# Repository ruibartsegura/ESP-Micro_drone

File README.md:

# ESP Micro Drone
## Intro
Development of a micro drone based on an ESP platform, adapted and extended through the integration of ROS 2. It uses an ESP32-S2 mini as flight controller and talks to a ROS 2 computer over WiFi with micro-ROS. </br>

</br>

## Repository

| Folder | What it is |
|--------|------------|
| [`code/`](https://github.com/ruibartsegura/ESP-Micro_drone/tree/main/code) | Firmware of the ESP32-S2 (ESP-IDF + micro-ROS), host unit tests and the ROS 2 workspace. |
| [`PCB_design/`](https://github.com/ruibartsegura/ESP-Micro_drone/tree/main/PCB_design) | KiCad project of the drone PCB, with the files to manufacture it. |
| `Hardware_Design/` | FreeCAD models of the frame, motors, blades and the complete drone. |
| `img/` | Images used in the READMEs. |

## [PCB Design](https://github.com/ruibartsegura/ESP-Micro_drone/tree/main/PCB_design)
The PCB is the frame of the drone. The ESP32-S2 mini and a GY-87 sensor board (MPU-6050 + BMP180) are plugged into it, and it has the drivers of the 4 motors, the 3.3 V regulator, the battery connector and the status LEDs.

## [Code](https://github.com/ruibartsegura/ESP-Micro_drone/tree/main/code)
The firmware runs every part of the drone as a FreeRTOS task: sensors, state machine, cascade PID controller, odometry and the micro-ROS node. The same firmware can also fly a simulated drone in Gazebo, so the controller can be tested before flying the real one. See [`code/README.md`](code/README.md) to build, flash and fly it.

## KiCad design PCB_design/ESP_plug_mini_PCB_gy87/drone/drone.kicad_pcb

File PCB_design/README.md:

# PCB design

Here you can find the design of the drone PCB, made with KiCad.

## [Plug mini PCB (GY-87)](https://github.com/ruibartsegura/ESP-Micro_drone/tree/main/PCB_design/ESP_plug_mini_PCB_gy87/drone)

The PCB is also the frame of the drone. The boards are not soldered on it, they are plugged in:

- **ESP32-S2 mini** (Wemos S2 Mini), on two 2x8 pin sockets.
- **GY-87** sensor board, on a 1x8 header. The firmware uses its MPU-6050 (accelerometer + gyroscope) and its BMP180 (barometer).

The board also has:

- 4 MOSFET drivers (AO3400A) for the motors.
- 3.3 V regulator (AP2112K-3.3).
- JST-PH connector for the battery.
- Status LEDs and a push button.

### Files

| File | What it is |
|------|------------|
| `drone.kicad_pro`, `drone.kicad_sch`, `drone.kicad_pcb` | KiCad project, schematic and PCB. |
| `*.pretty/`, `fp-lib-table` | Custom footprints used by the PCB. |
| `production/` | Files to manufacture it: Gerbers (`production/drone/`), `BOM.csv`, pick and place (`drone-all.pos`) and the 3D model (`drone.step`). |

The 3D models of the ESP32-S2 mini and the GY-87 are in [`extra_step_files/`](https://github.com/ruibartsegura/ESP-Micro_drone/tree/main/PCB_design/extra_step_files).

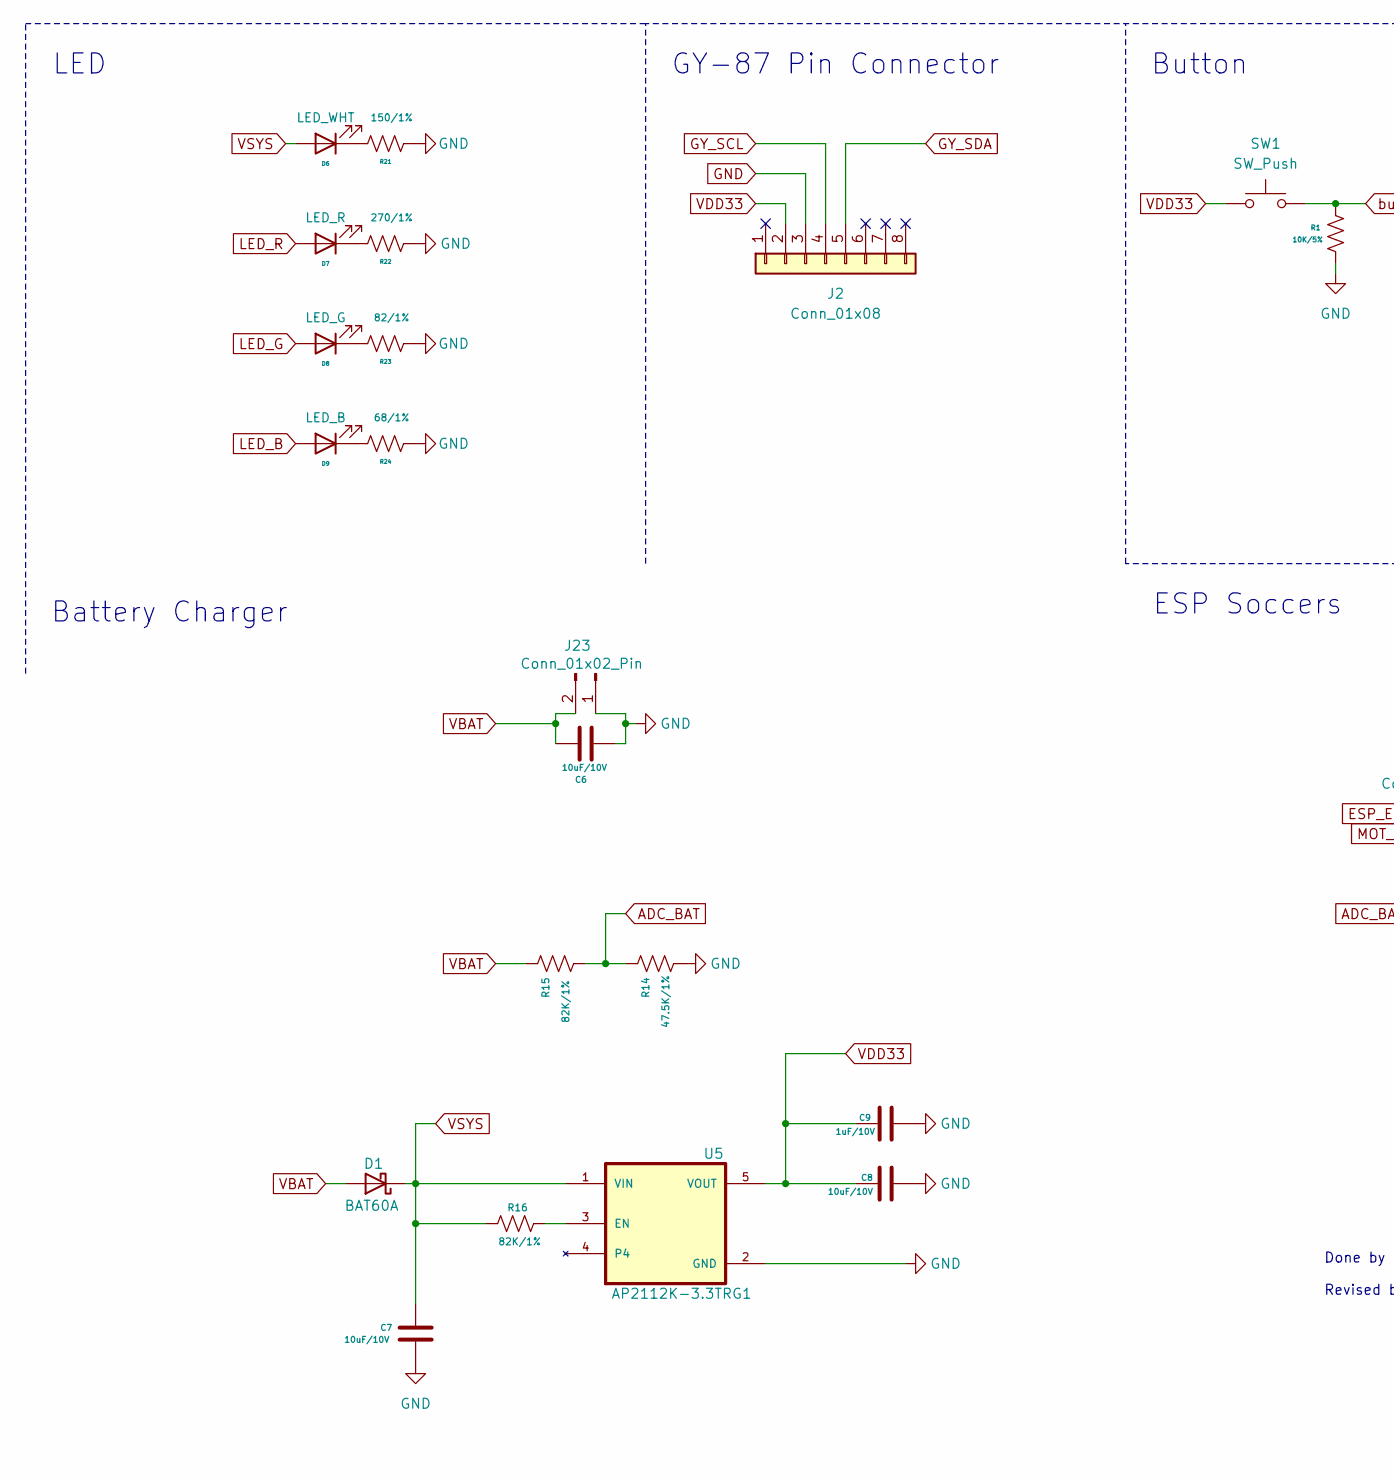
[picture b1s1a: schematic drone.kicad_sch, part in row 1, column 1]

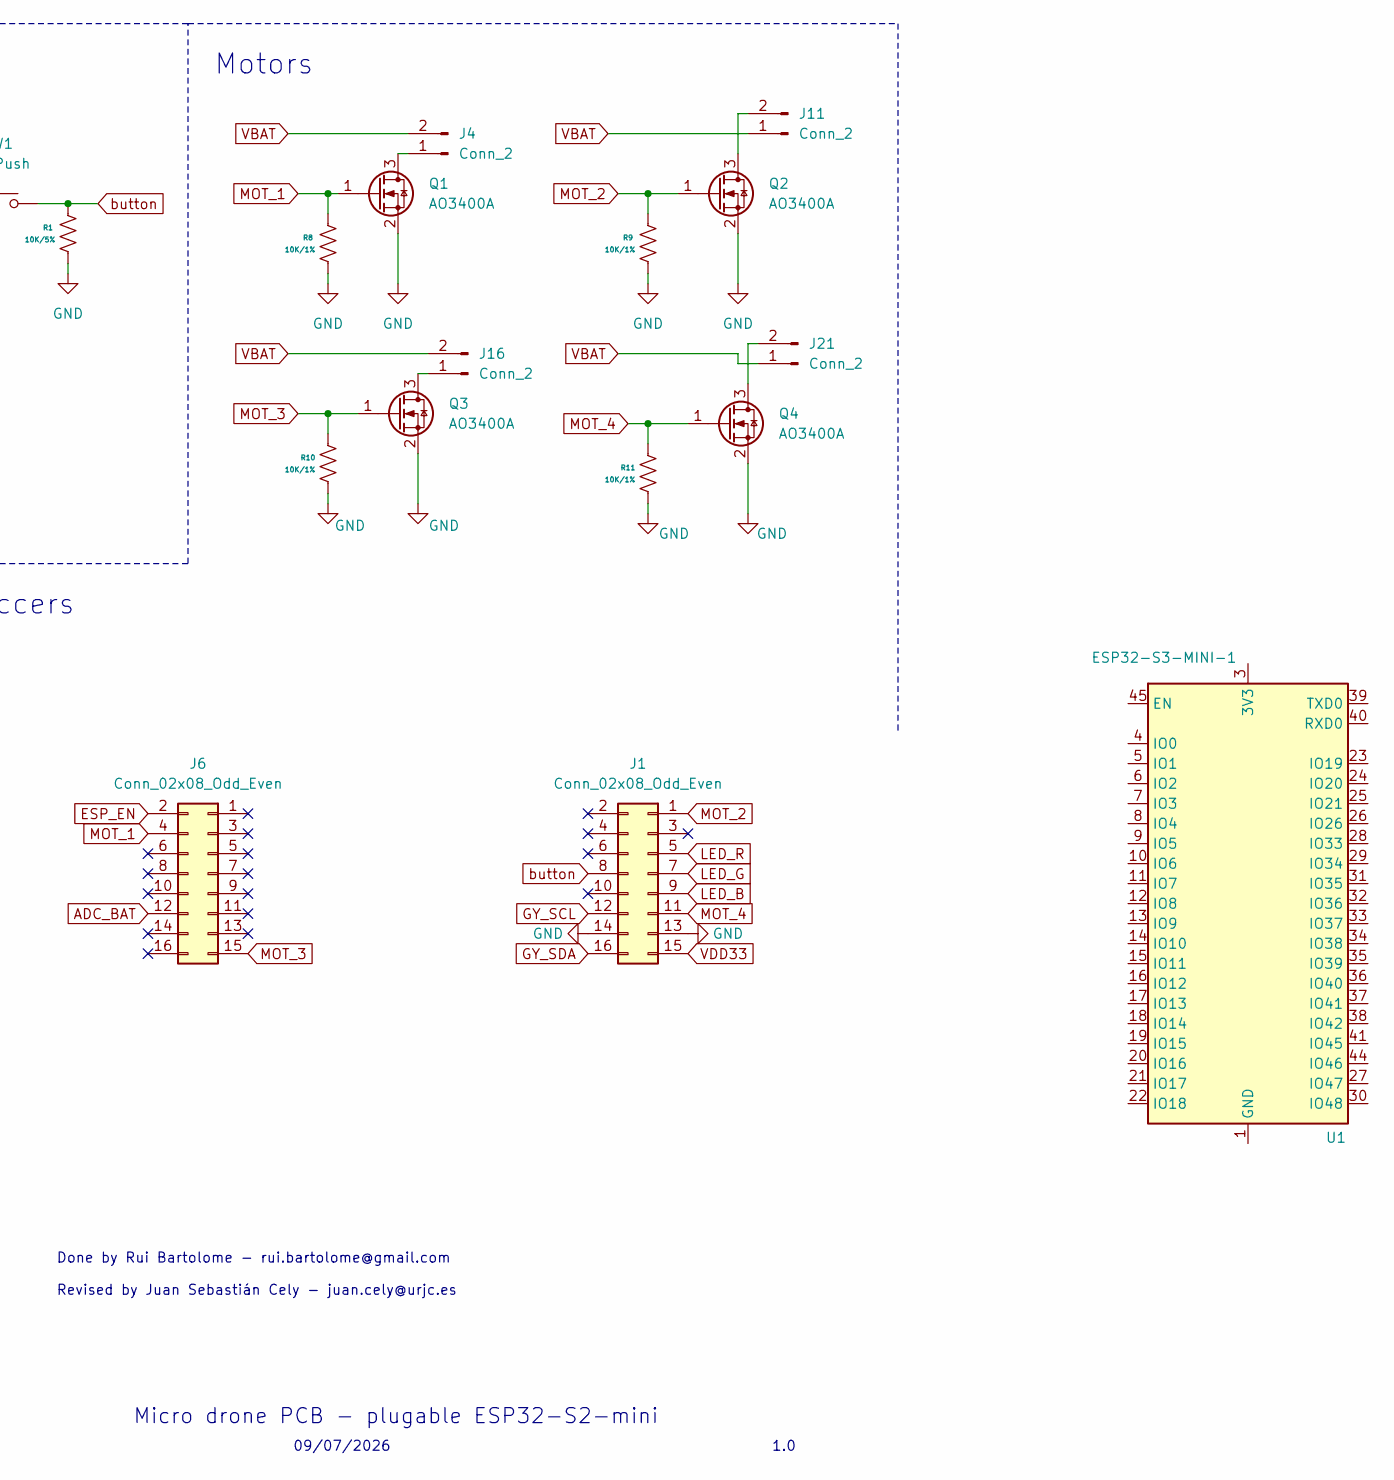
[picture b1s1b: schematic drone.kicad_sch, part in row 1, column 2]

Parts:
C6, C7, C8: 10uF/10V; C_0603_1608Metric
C9: 1uF/10V; C_0201_0603Metric
D1: BAT60A; D_SOD-323
D6: LED_WHT; LED_0201_0603Metric
D7: LED_R; LED_0201_0603Metric
D8: LED_G; LED_0201_0603Metric
D9: LED_B; LED_0201_0603Metric
J1, J6: Conn_02x08_Odd_Even; PinSocket_2x08_P2.54mm_Vertical
J2: Conn_01x08; PinHeader_1x08_P2.54mm_Vertical
J4, J11, J16, J21: Conn_2; JST_XH_S2B-XH-A-1_1x02_P2.50mm_Horizontal
J23: Conn_01x02_Pin; JST_PH_S2B-PH-K_1x02_P2.00mm_Horizontal
Q1, Q2, Q3, Q4: AO3400A; SOT-23
R1: 10K/5%; R_0201_0603Metric
R8, R9, R10, R11: 10K/1%; R_0201_0603Metric
R14: 47.5K/1%; R_0402_1005Metric
R15, R16: 82K/1%; R_0603_1608Metric
R21: 150/1%; R_0201_0603Metric
R22: 270/1%; R_0201_0603Metric
R23: 82/1%; R_0201_0603Metric
R24: 68/1%; R_0201_0603Metric
SW1: SW_Push; SW_SPST_B3U-1000P
U1: ESP32-S3-MINI-1
U5: AP2112K-3.3TRG1; PARTREV 2-2

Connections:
ADC_BAT: J6.12, R14.2, R15.1
ESP_EN: J6.2
GND: C6.1, C7.1, C8.1, C9.1, J1.13, J1.14, J2.3, J23.1, Q1.2 (S), Q2.2 (S), Q3.2 (S), Q4.2 (S), R1.2, R8.2, R9.2, R10.2, R11.2, R14.1, R21.1, R22.1, R23.1, R24.1, U5.2 (GND)
GY_SCL: J1.12, J2.4
GY_SDA: J1.16, J2.5
LED_B: D9.2 (A), J1.9
LED_G: D8.2 (A), J1.7
LED_R: D7.2 (A), J1.5
MOT_1: J6.4, Q1.1 (G), R8.1
MOT_2: J1.1, Q2.1 (G), R9.1
MOT_3: J6.15, Q3.1 (G), R10.1
MOT_4: J1.11, Q4.1 (G), R11.1
unnamed: D6.1 (K), R21.2
unnamed: D7.1 (K), R22.2
unnamed: D8.1 (K), R23.2
unnamed: D9.1 (K), R24.2
unnamed: J4.1, Q1.3 (D)
unnamed: J11.2, Q2.3 (D)
unnamed: J16.1, Q3.3 (D)
unnamed: J21.2, Q4.3 (D)
unnamed: R16.2, U5.3 (EN)
VBAT: C6.2, D1.2 (A), J4.2, J11.1, J16.2, J21.1, J23.2, R15.2
VDD33: C8.2, C9.2, J1.15, J2.2, SW1.1, U5.5 (VOUT)
VSYS: C7.2, D1.1 (K), D6.2 (A), R16.1, U5.1 (VIN)
button: J1.8, R1.1, SW1.2

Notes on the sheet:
Button
Micro drone PCB - plugable ESP32-S2-mini
Battery Charger
GY-87 Pin Connector
Done by Rui Bartolome - rui.bartolome@gmail.com Revised by Juan Sebastián Cely - juan.cely@urjc.es
LED
1.0
09/07/2026
Motors
ESP Soccers

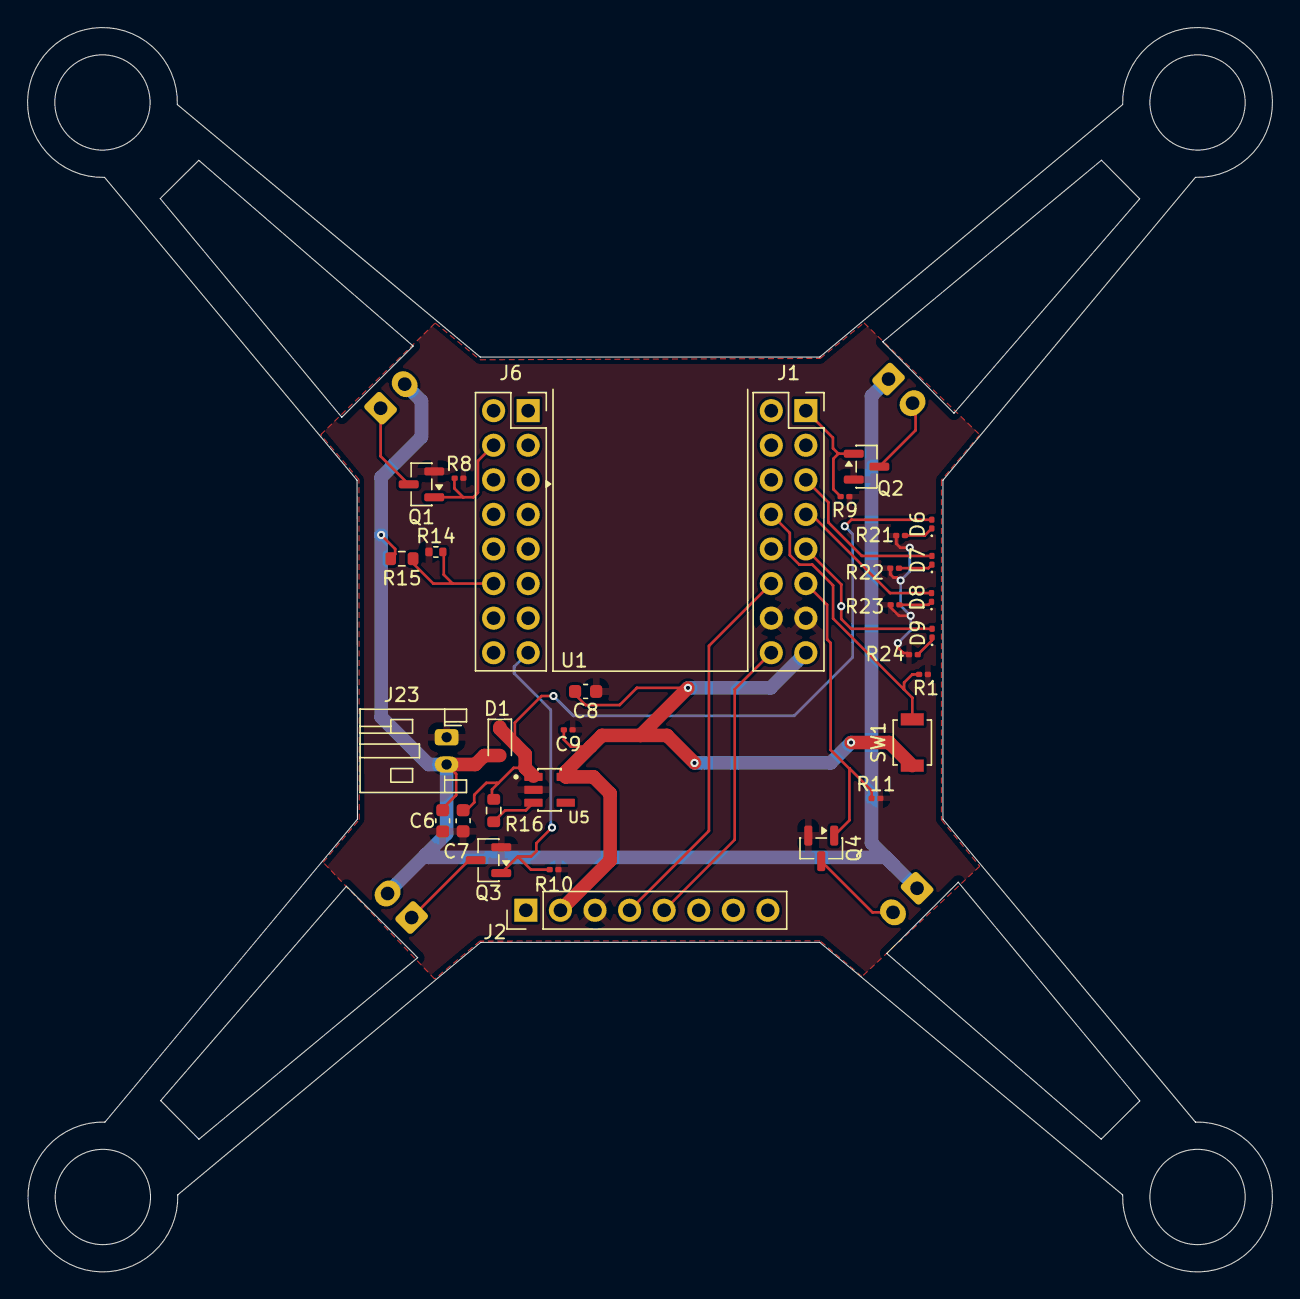
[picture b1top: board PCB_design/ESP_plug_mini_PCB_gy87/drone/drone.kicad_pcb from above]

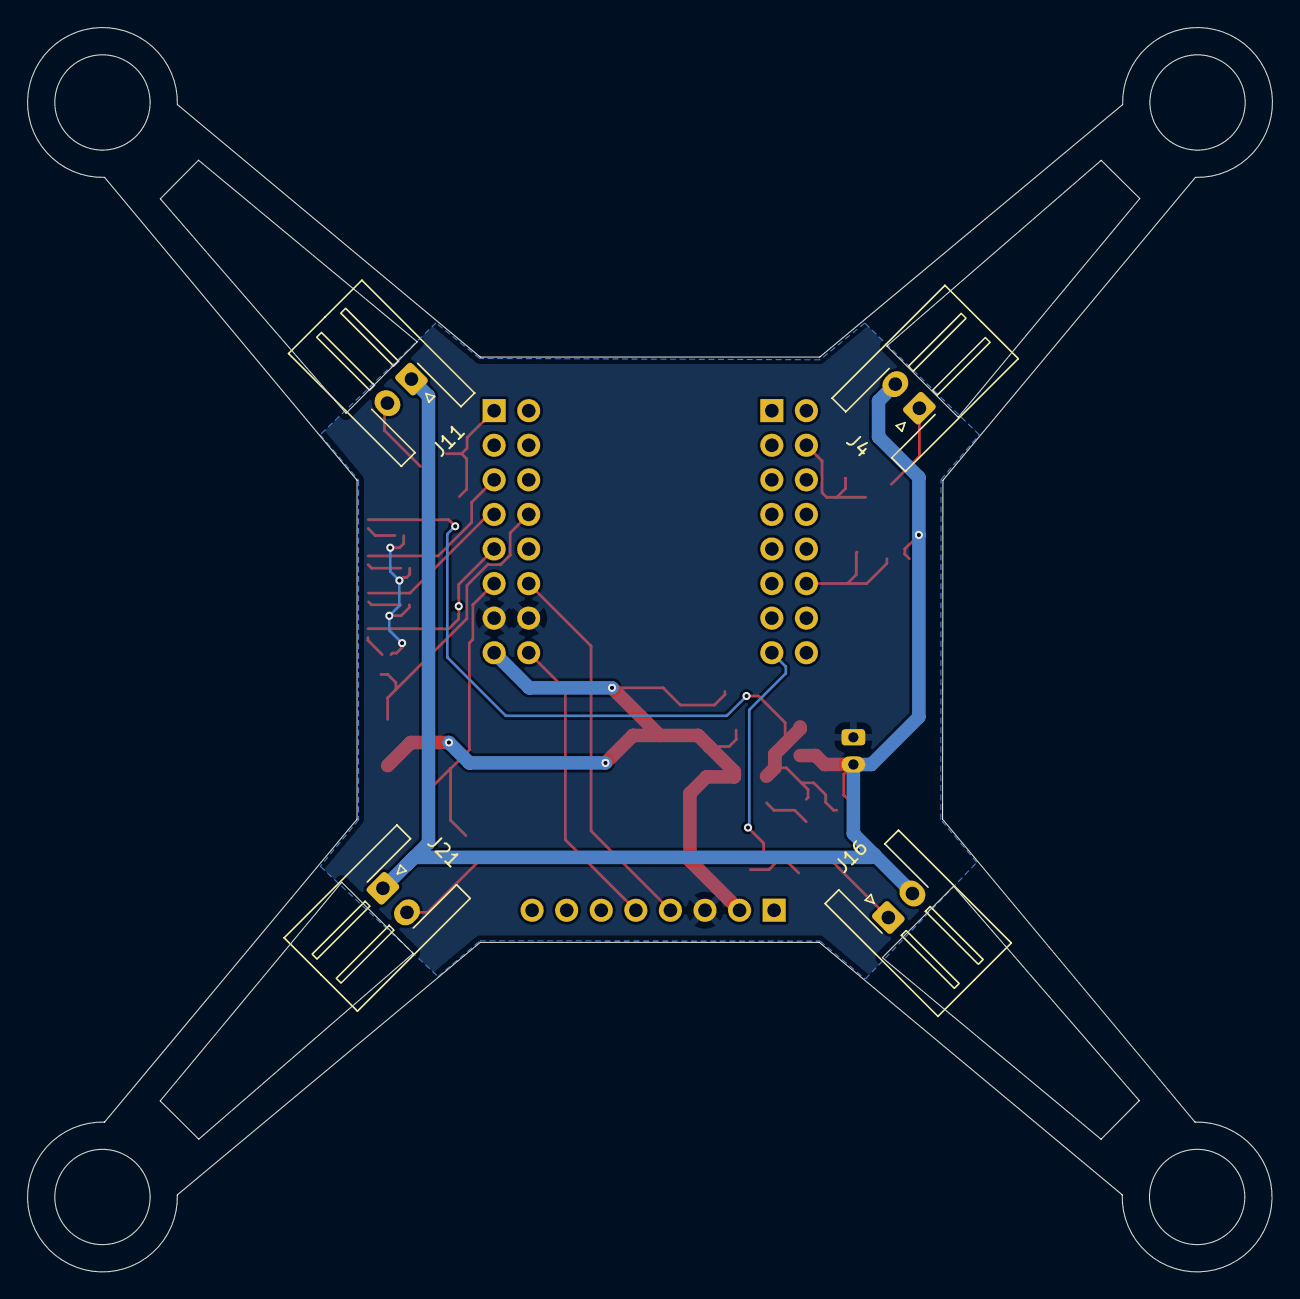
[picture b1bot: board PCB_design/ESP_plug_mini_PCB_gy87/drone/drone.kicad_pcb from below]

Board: 2 copper layers, 91.5 x 91.4 mm, 36 parts (4 on the bottom side), 24 nets.

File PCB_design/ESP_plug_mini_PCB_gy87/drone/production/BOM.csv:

Id,Designator,Footprint,Quantity,Designation,Supplier and ref
1,SW1,SW_SPST_B3U-1000P,1,SW_Push,
2,R1,R_0201_0603Metric,1,10K/5%,
3,"C7,C6,C8",C_0603_1608Metric,3,10uF/10V,
4,D9,LED_0201_0603Metric,1,LED_B,
5,"Q3,Q1,Q2,Q4",SOT-23,4,AO3400A,
6,"R9,R10,R8,R11",R_0201_0603Metric,4,10K/1%,
7,R14,R_0402_1005Metric,1,47.5K/1%,
8,C9,C_0201_0603Metric,1,1uF/10V,
10,D1,D_SOD-323,1,BAT60A,
11,"R16,R15",R_0603_1608Metric,2,82K/1%,
12,J23,JST_PH_S2B-PH-K_1x02_P2.00mm_Horizontal,1,Conn_01x02_Pin,
13,R22,R_0201_0603Metric,1,270/1%,
14,"J1,J6",PinSocket_2x08_P2.54mm_Vertical,2,Conn_02x08_Odd_Even,
15,R24,R_0201_0603Metric,1,68/1%,
16,J2,PinHeader_1x08_P2.54mm_Vertical,1,Conn_01x08,
17,R23,R_0201_0603Metric,1,82/1%,
18,D8,LED_0201_0603Metric,1,LED_G,
19,R21,R_0201_0603Metric,1,150/1%,
20,D6,LED_0201_0603Metric,1,LED_WHT,
21,D7,LED_0201_0603Metric,1,LED_R,
22,U5,AP2112K-3.3TRG1,1,AP2112K-3.3TRG1,
23,"J4,J11,J16,J21",JST_XH_S2B-XH-A-1_1x02_P2.50mm_Horizontal,4,Conn_2,

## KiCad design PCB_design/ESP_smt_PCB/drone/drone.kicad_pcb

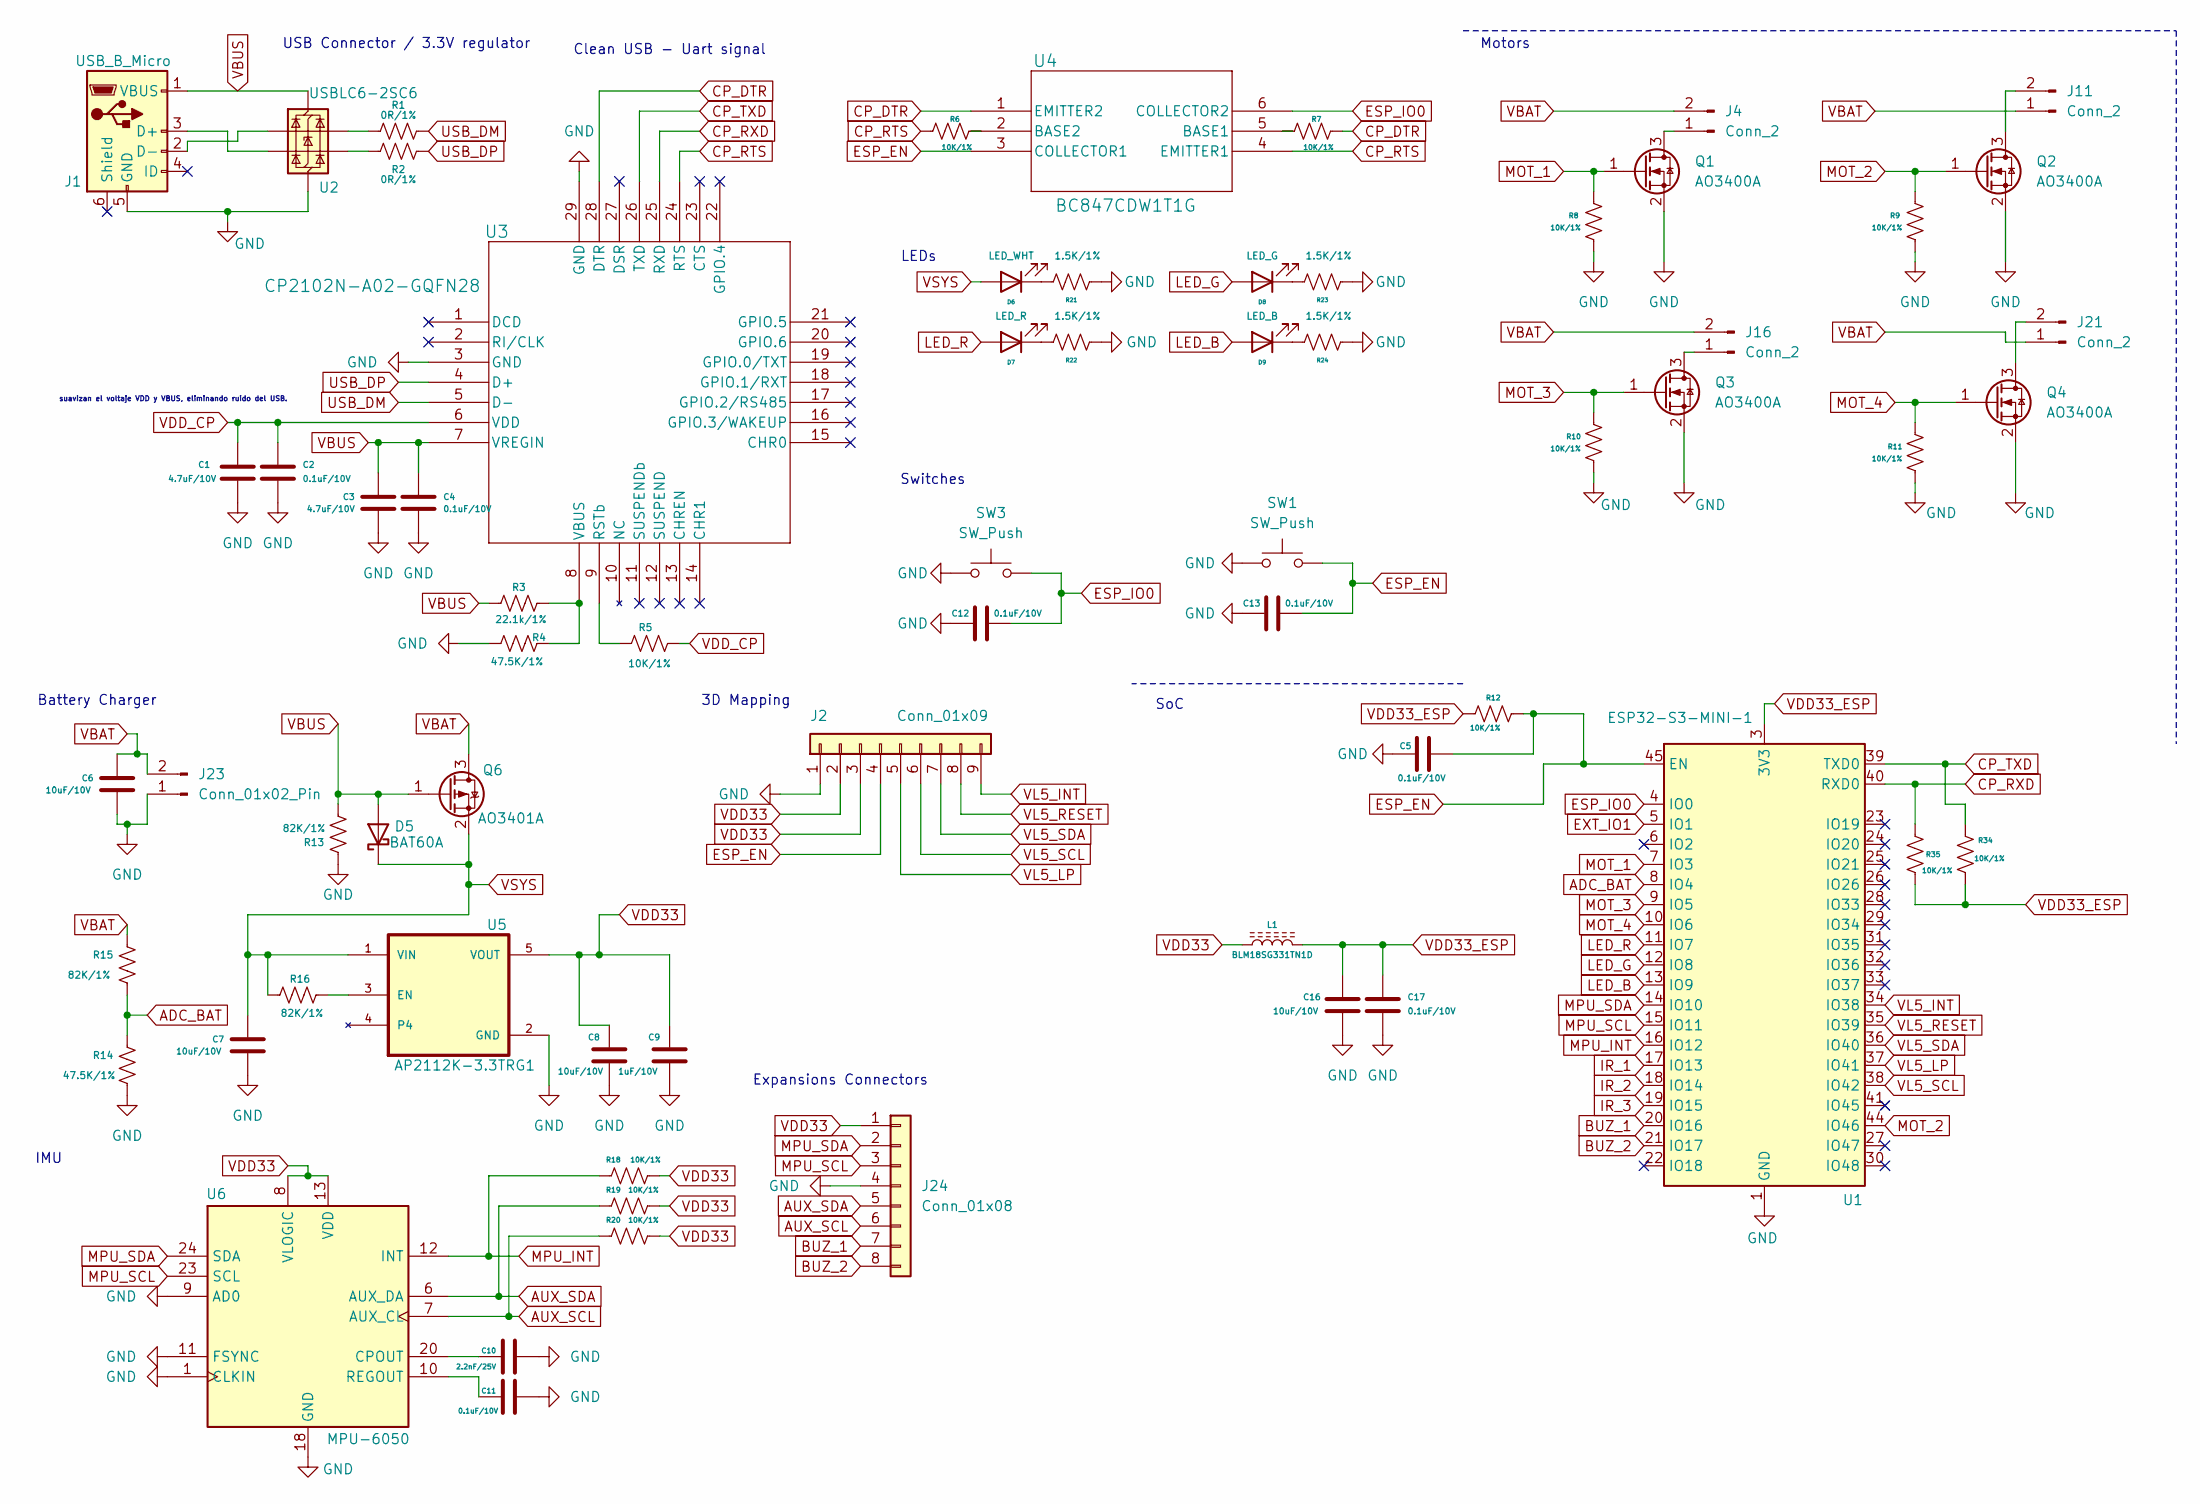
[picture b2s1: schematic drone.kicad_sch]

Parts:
C1, C3: 4.7uF/10V; C_0201_0603Metric
C2, C4, C5, C11, C12, C13, C17: 0.1uF/10V; C_0201_0603Metric
C6, C7, C8, C16: 10uF/10V; C_0201_0603Metric
C9: 1uF/10V; C_0201_0603Metric
C10: 2.2nF/25V; C_0201_0603Metric
D5: BAT60A; D_SOD-323
D6: LED_WHT; LED_0201_0603Metric
D7: LED_R; LED_0201_0603Metric
D8: LED_G; LED_0201_0603Metric
D9: LED_B; LED_0201_0603Metric
J1: USB_B_Micro; USB_Micro-B_Amphenol_10118193-0002LF_Horizontal
J2: Conn_01x09; PinSocket_1x09_P2.54mm_Horizontal
J4, J11, J16, J21: Conn_2; JST_XH_S2B-XH-A-1_1x02_P2.50mm_Horizontal
J23: Conn_01x02_Pin; JST_PH_S2B-PH-K_1x02_P2.00mm_Horizontal
J24: Conn_01x08; JST_PH_B8B-PH-K_1x08_P2.00mm_Vertical
L1: BLM18SG331TN1D; L_0201_0603Metric
Q1, Q2, Q3, Q4: AO3400A; SOT-23
Q6: AO3401A; SOT-23
R1, R2: 0R/1%; R_0201_0603Metric
R3: 22.1k/1%; R_0201_0603Metric
R4, R14: 47.5K/1%; R_0201_0603Metric
R5, R6, R7, R8, R9, R10, R11, R12, R18, R19, R20, R34, R35: 10K/1%; R_0201_0603Metric
R13, R15, R16: 82K/1%; R_0201_0603Metric
R21, R22, R23, R24: 1.5K/1%; R_0201_0603Metric
SW1, SW3: SW_Push; SW_DIP_SPSTx01_Slide_6.7x4.1mm_W8.61mm_P2.54mm_LowProfile
U1: ESP32-S3-MINI-1; ESP32-S2-MINI-1
U2: USBLC6-2SC6; SOT-23-6
U3: CP2102N-A02-GQFN28
U4: BC847CDW1T1G
U5: AP2112K-3.3TRG1; PARTREV 2-2
U6: MPU-6050; InvenSense_QFN-24_4x4mm_P0.5mm

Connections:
ADC_BAT: R14.2, R15.1, U1.8 (IO4)
AUX_SCL: J24.6, R20.2, U6.7 (AUX_CL)
AUX_SDA: J24.5, R19.2, U6.6 (AUX_DA)
BUZ_1: J24.7, U1.20 (IO16)
BUZ_2: J24.8, U1.21 (IO17)
CP_DTR: R7.1, U3.28 (DTR), U4.1 (EMITTER2)
CP_RTS: R6.2, U3.24 (RTS), U4.4 (EMITTER1)
CP_RXD: R35.2, U1.40 (RXD0), U3.25 (RXD)
CP_TXD: R34.2, U1.39 (TXD0), U3.26 (TXD)
ESP_EN: C5.1, C13.1, J2.4, R12.2, SW1.2, U1.45 (EN), U4.3 (COLLECTOR1)
ESP_IO0: C12.1, SW3.2, U1.4 (IO0), U4.6 (COLLECTOR2)
EXT_IO1: U1.5 (IO1)
GND: C1.2, C2.2, C3.1, C4.2, C5.2, C6.1, C7.1, C8.1, C9.1, C10.1, C11.1, C12.2, C13.2, C16.2, C17.2, J1.5 (GND), J2.1, J23.1, J24.4, Q1.2 (S), Q2.2 (S), Q3.2 (S), Q4.2 (S), R4.2, R8.2, R9.2, R10.2, R11.2, R13.1, R14.1, R21.1, R22.1, R23.1, R24.1, SW1.1, SW3.1, U1.1 (GND), U1.2 (GND), U1.42 (GND), U1.43 (GND), U1.46 (GND), U1.47 (GND), U1.48 (GND), U1.49 (GND), U1.50 (GND), U1.51 (GND), U1.52 (GND), U1.53 (GND), U1.54 (GND), U1.55 (GND), U1.56 (GND), U1.57 (GND), U1.58 (GND), U1.59 (GND), U1.60 (GND), U1.61 (GND), U1.62 (GND), U1.63 (GND), U1.64 (GND), U1.65 (GND), U2.2 (GND), U3.3 (GND), U3.29 (GND), U5.2 (GND), U6.1 (CLKIN), U6.9 (AD0), U6.11 (FSYNC), U6.18 (GND)
IR_1: U1.17 (IO13)
IR_2: U1.18 (IO14)
IR_3: U1.19 (IO15)
LED_B: D9.2 (A), U1.13 (IO9)
LED_G: D8.2 (A), U1.12 (IO8)
LED_R: D7.2 (A), U1.11 (IO7)
MOT_1: Q1.1 (G), R8.1, U1.7 (IO3)
MOT_2: Q2.1 (G), R9.1, U1.44 (IO46)
MOT_3: Q3.1 (G), R10.1, U1.9 (IO5)
MOT_4: Q4.1 (G), R11.1, U1.10 (IO6)
MPU_INT: R18.2, U1.16 (IO12), U6.12 (INT)
MPU_SCL: J24.3, U1.15 (IO11), U6.23 (SCL)
MPU_SDA: J24.2, U1.14 (IO10), U6.24 (SDA)
unnamed: D6.1 (K), R21.2
unnamed: D7.1 (K), R22.2
unnamed: D8.1 (K), R23.2
unnamed: D9.1 (K), R24.2
unnamed: J1.3 (D+), U2.3 (I/O2)
unnamed: J1.2 (D-), U2.1 (I/O1)
unnamed: J4.1, Q1.3 (D)
unnamed: J11.2, Q2.3 (D)
unnamed: J16.1, Q3.3 (D)
unnamed: J21.2, Q4.3 (D)
unnamed: R1.1, U2.6 (I/O1)
unnamed: R2.2, U2.4 (I/O2)
unnamed: R5.1, U3.9 (RSTb)
unnamed: R3.2, R4.1, U3.8 (VBUS)
unnamed: R7.2, U4.5 (BASE1)
unnamed: R6.1, U4.2 (BASE2)
unnamed: R16.2, U5.3 (EN)
unnamed: C10.2, U6.20 (CPOUT)
unnamed: C11.2, U6.10 (REGOUT)
USB_DM: R1.2, U3.5 (D-)
USB_DP: R2.1, U3.4 (D+)
VBAT: C6.2, J4.2, J11.1, J16.2, J21.1, J23.2, Q6.3 (D), R15.2
VBUS: C3.2, C4.1, D5.2 (A), J1.1 (VBUS), Q6.1 (G), R3.1, R13.2, U2.5 (VBUS), U3.7 (VREGIN)
VDD33: C8.2, C9.2, J2.2, J2.3, J24.1, L1.1, R18.1, R19.1, R20.1, U5.5 (VOUT), U6.8 (VLOGIC), U6.13 (VDD)
VDD33_ESP: C16.1, C17.1, L1.2, R12.1, R34.1, R35.1, U1.3 (3V3)
VDD_CP: C1.1, C2.1, R5.2, U3.6 (VDD)
VL5_INT: J2.9, U1.34 (IO38)
VL5_LP: J2.5, U1.37 (IO41)
VL5_RESET: J2.8, U1.35 (IO39)
VL5_SCL: J2.6, U1.38 (IO42)
VL5_SDA: J2.7, U1.36 (IO40)
VSYS: C7.2, D5.1 (K), D6.2 (A), Q6.2 (S), R16.1, U5.1 (VIN)

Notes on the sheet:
Switches
Expansions Connectors
IMU
Battery Charger
LEDs
USB Connector / 3.3V regulator
Clean USB - Uart signal
Motors
suavizan el voltaje VDD y VBUS, eliminando ruido del USB.
SoC
3D Mapping

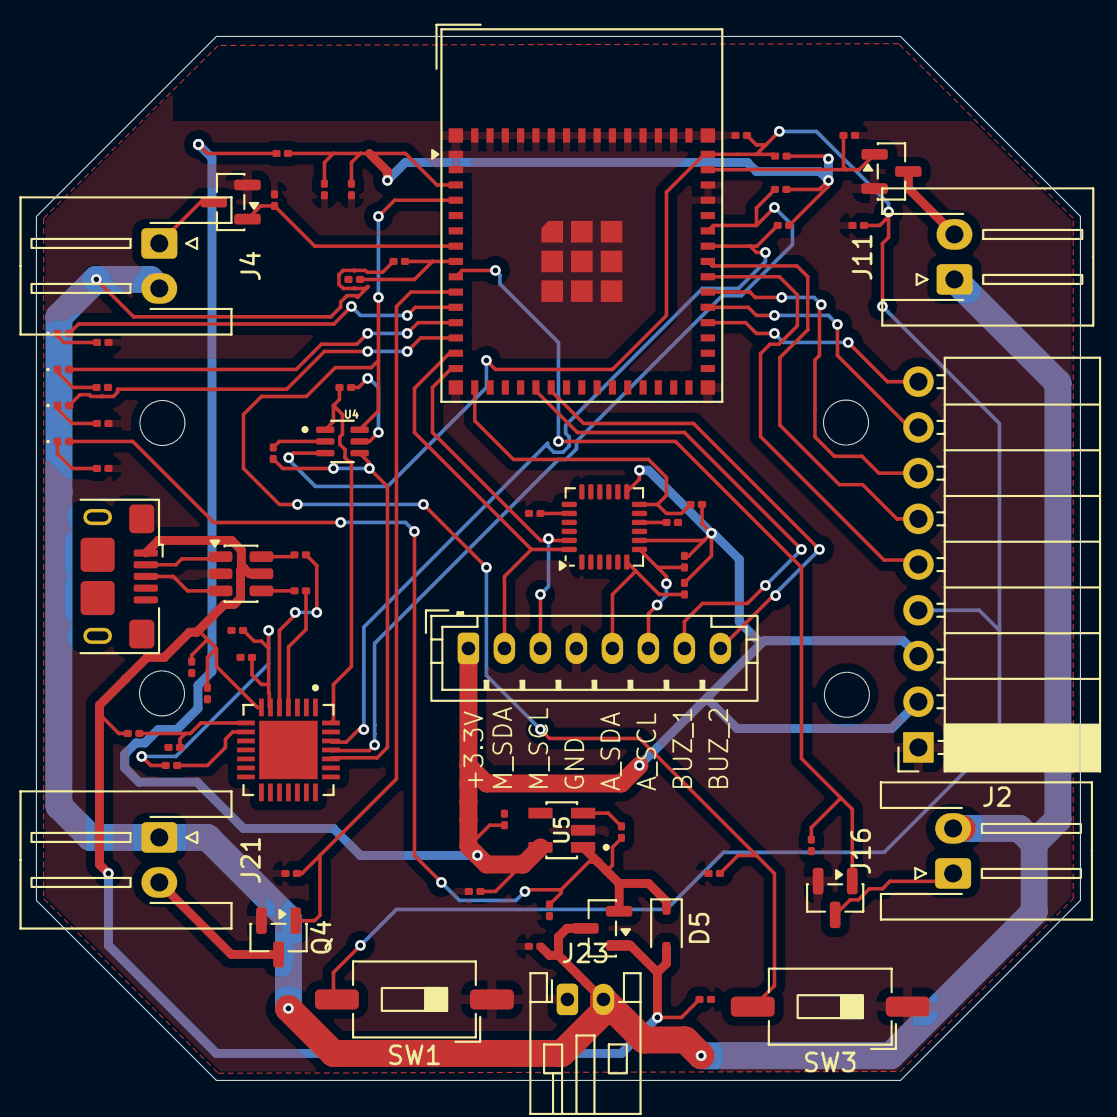
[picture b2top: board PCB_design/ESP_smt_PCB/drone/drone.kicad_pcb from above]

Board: 2 copper layers, 58.0 x 58.0 mm, 67 parts (0 on the bottom side), 54 nets.

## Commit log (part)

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2026-03-26 initial commit - hardware
2026-03-28 Holes in the pcb
2026-03-28 Pcb with holes
2026-03-28 Add project overview and PCB design information
    Added introductory information and PCB design details for the ESP Micro Drone project.
2026-03-28 3d models and images
2026-03-28 Rename img/Screenshot from 2026-03-28 18-08-57.png to pcb_smt.png
2026-03-28 Rename pcv_smt.png to pcb_smt.png
2026-03-28 change names
2026-03-28 Enhance README with images and layout for PCB design
    Added images and table layout for PCB designs.
2026-04-16 Fix 3.3v
2026-04-18 schematics img
2026-04-18 readme
2026-05-03 fix pcb plug
2026-05-12 pcb mini
2026-05-12 img mini pcb
2026-06-01 pcb updated
